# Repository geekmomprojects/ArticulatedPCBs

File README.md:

# Articulated PCBs (aka "Bendy Boards")
Design files and BOM for an articulated assembly of PCBs comprised of two-layered links that can pivot around a vertical axis, allowing the assembly to bend at every joint while still maintaining electrical contact between all of the boards in the assembly.<BR>

A demonstration of the boards and the assembly is on <a href="https://www.youtube.com/watch?v=9HDyzVgGNhk">YouTube:<BR> 
</a>

The two layers of each link connect through pressure connectors on the bottom PCB which make contact with cocentric ring-shaped pads on the top one. A laser-cut buffer layer of 1.6mm (1/16") acrylic between the two PCBs prevents the connectors from being crushed. The connectors have a working height of 1.7 mm, which prevents the connectors from being crushed between the PCBs. The layers in the link are held together with an M3 nylon push rivet. Vertical board-to-board snap connectors connect each link to the previous one in the chain. The mating height of these snap connectors is about 1.5 mm, so the spacing between the PCB layers is the same everywhere.<BR>

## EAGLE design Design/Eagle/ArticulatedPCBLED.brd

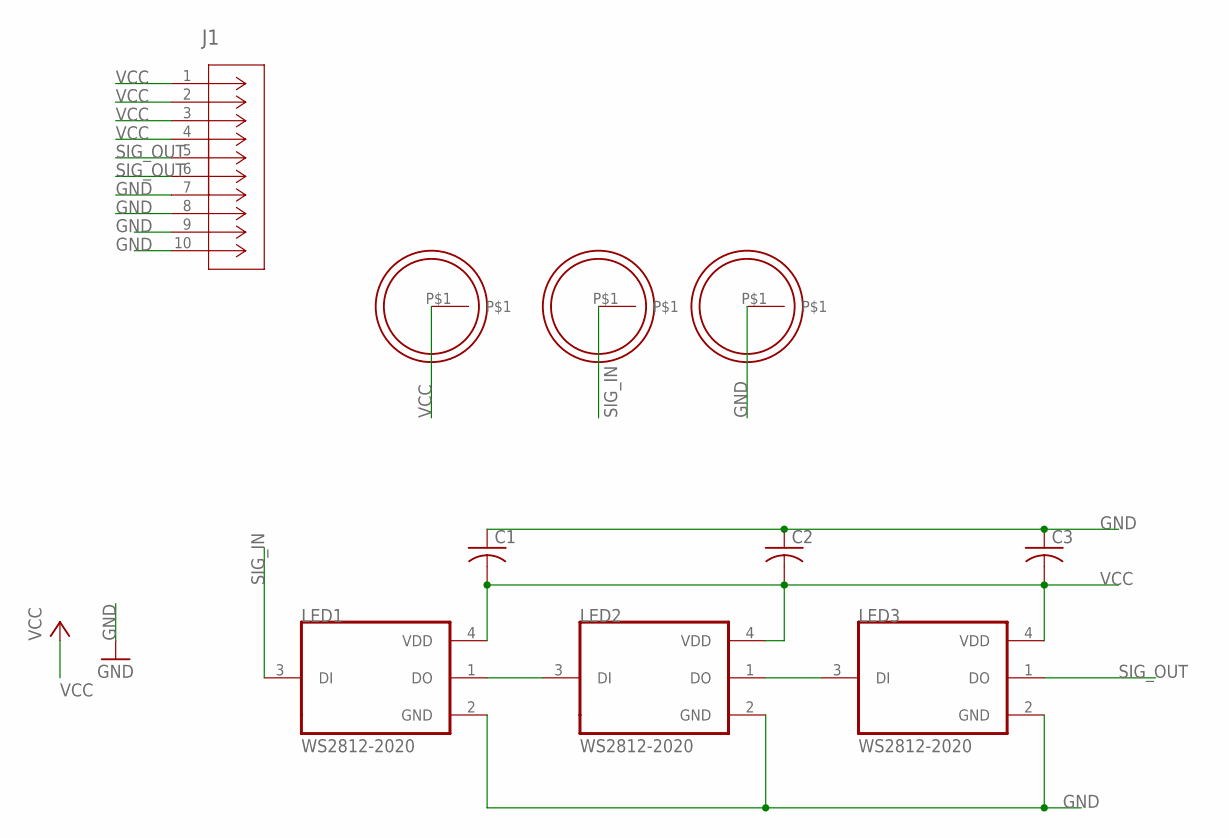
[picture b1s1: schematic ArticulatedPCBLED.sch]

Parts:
C1, C2, C3: C-USC0603; C0603
J1: DF23C-10DP-0.5V(92); CONN_DF23C-10DP-0.5V(92)_HIR
LED1, LED2, LED3: WS2812-2020; LED_WS2812-2020
U$2: CIRCLE_PAD_17_2_OD
U$3: CIRCLE_PAD_8_2_OD
U$4: CIRCLE_PAD_12_7_OD

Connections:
GND: C1.1, C2.1, C3.1, J1.7, J1.8, J1.9, J1.10, LED1.2 (GND), LED2.2 (GND), LED3.2 (GND), U$2.P$1
unnamed: LED1.1 (DO), LED2.3 (DI)
unnamed: LED2.1 (DO), LED3.3 (DI)
SIG_IN: LED1.3 (DI), U$4.P$1
SIG_OUT: J1.5, J1.6, LED3.1 (DO)
VCC: C1.2, C2.2, C3.2, J1.1, J1.2, J1.3, J1.4, LED1.4 (VDD), LED2.4 (VDD), LED3.4 (VDD), U$3.P$1

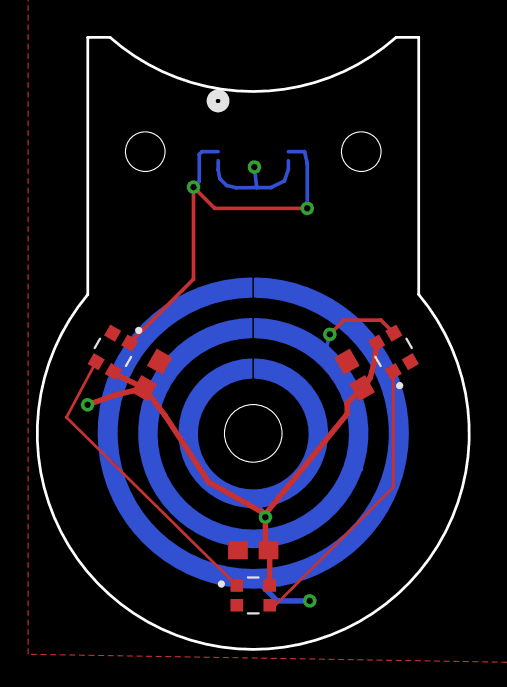
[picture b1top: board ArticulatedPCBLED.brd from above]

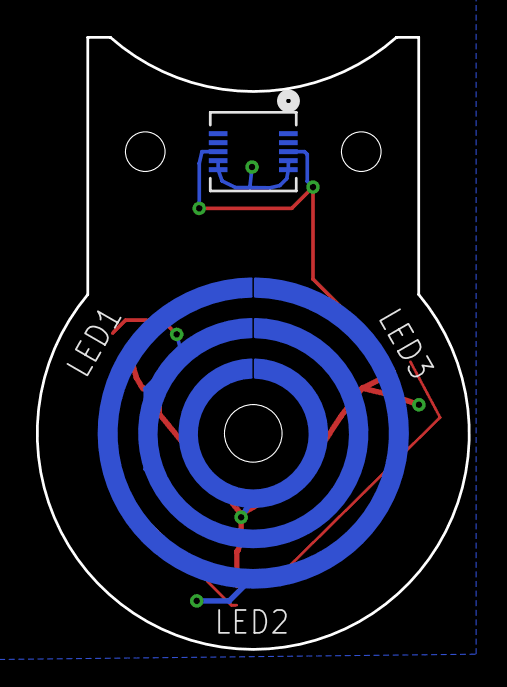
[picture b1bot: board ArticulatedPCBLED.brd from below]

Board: 2 copper layers, 24.0 x 34.0 mm, 10 parts (4 on the bottom side), 6 nets.

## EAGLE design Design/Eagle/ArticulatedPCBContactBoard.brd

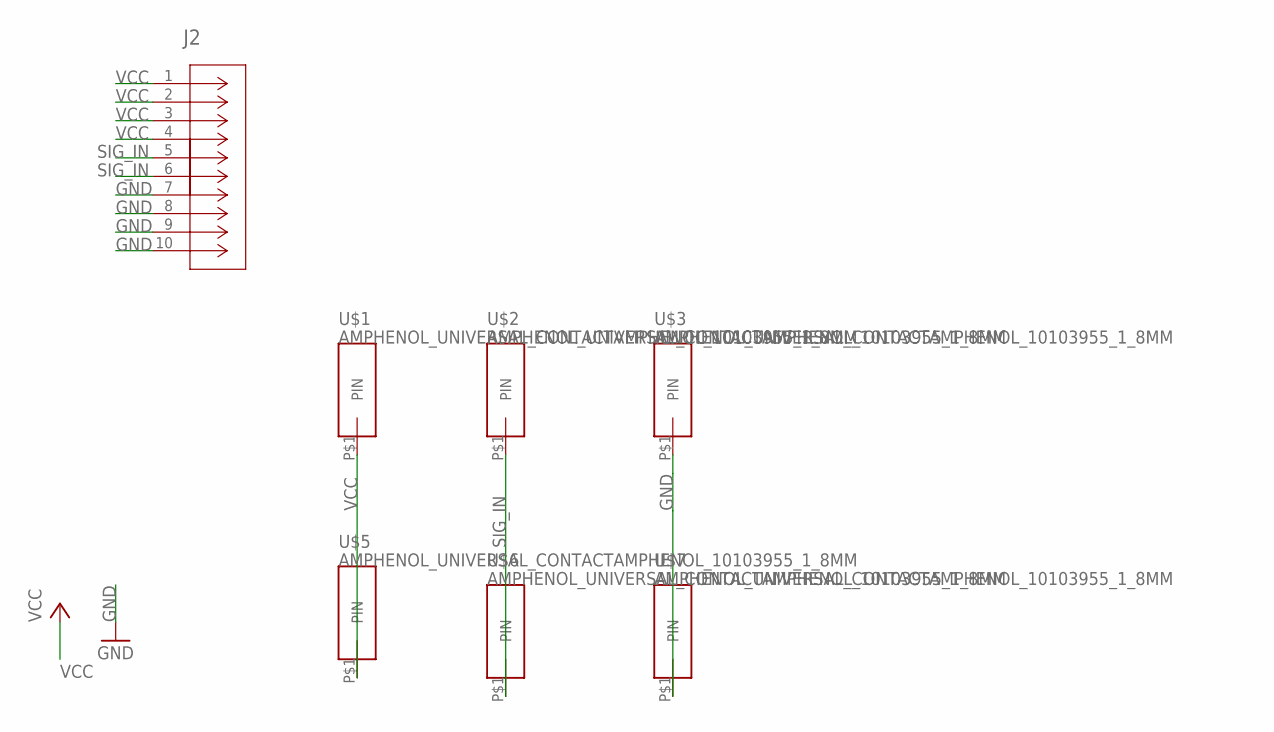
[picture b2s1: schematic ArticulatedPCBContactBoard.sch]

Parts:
J2: DF23C-10DS-0.5V(51); CONN_DF23C-10DS-0.5V(51)_HIR
U$1, U$2, U$3, U$5, U$6, U$7: AMPHENOL_UNIVERSAL_CONTACTAMPHENOL_10103955_1_8MM; AMPHENOL10103955

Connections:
GND: J2.7, J2.8, J2.9, J2.10, U$3.P$1, U$7.P$1
SIG_IN: J2.5, J2.6, U$2.P$1, U$6.P$1
VCC: J2.1, J2.2, J2.3, J2.4, U$1.P$1, U$5.P$1

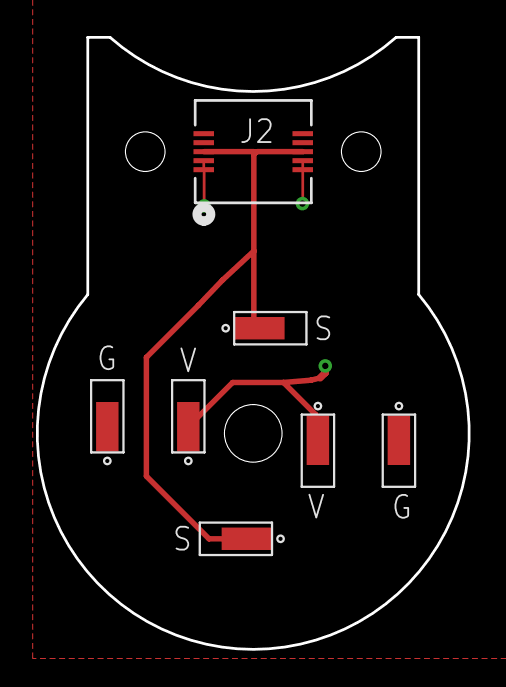
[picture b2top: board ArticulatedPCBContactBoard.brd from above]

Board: 2 copper layers, 24.0 x 34.0 mm, 7 parts (0 on the bottom side), 3 nets.

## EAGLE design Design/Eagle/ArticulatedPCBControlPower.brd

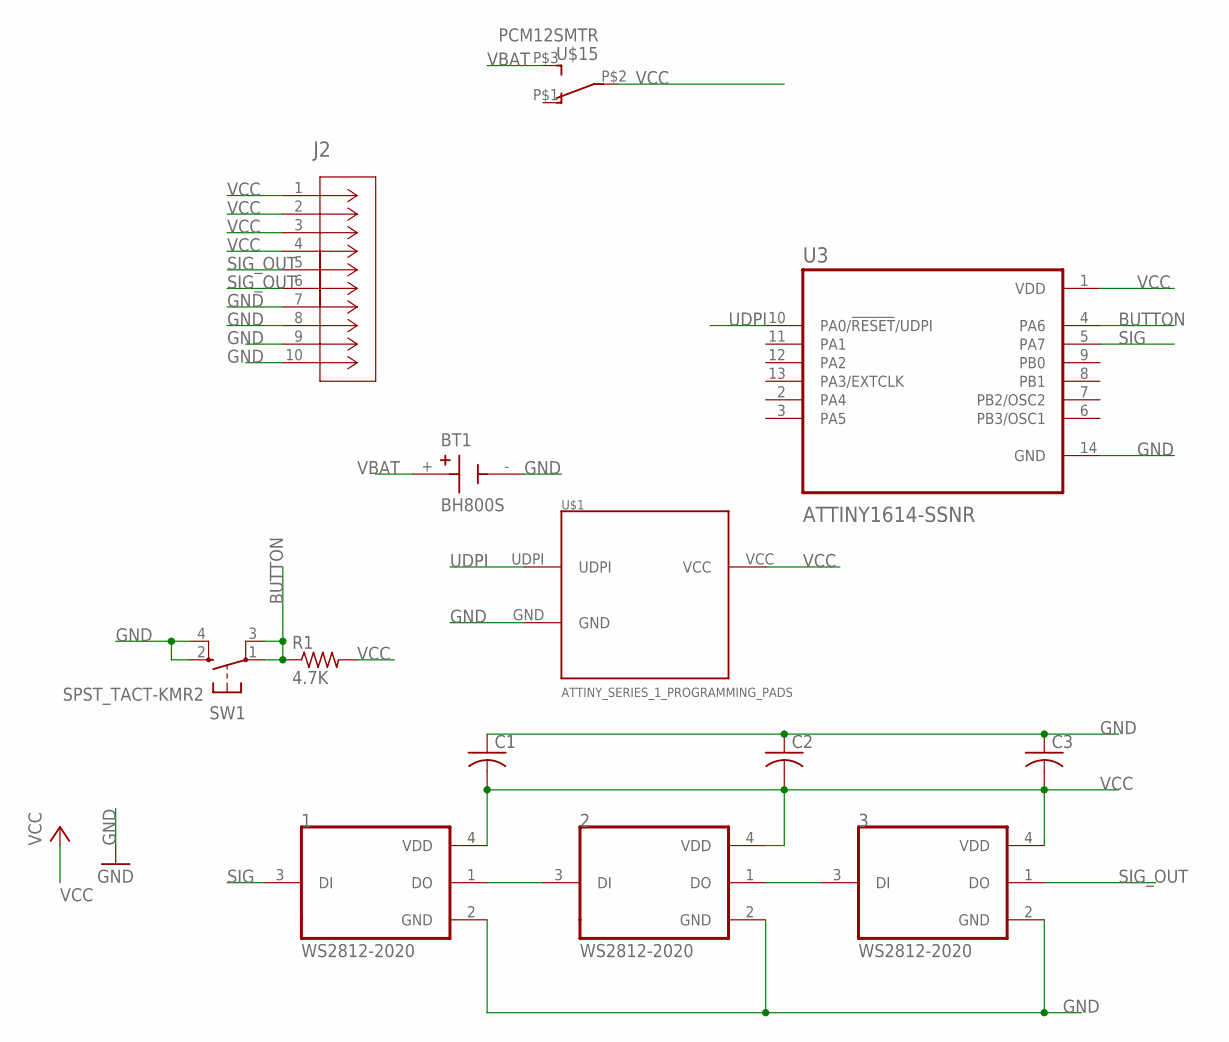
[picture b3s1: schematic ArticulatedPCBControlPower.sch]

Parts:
1, 2, 3: WS2812-2020; LED_WS2812-2020
BT1: BH800S; BAT_BH800S
C1, C2, C3: C-USC0603; C0603
J2: DF23C-10DP-0.5V(92); CONN_DF23C-10DP-0.5V(92)_HIR
R1: 4.7K; R0603
SW1: SPST_TACT-KMR2; KMR2
U3: ATTINY1614-SSNR; SOIC127P600X175-14N
U$1: ATTINY_SERIES_1_PROGRAMMING_PADS
U$15: PCM12SMTR

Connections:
BUTTON: R1.1, SW1.1, SW1.3 (P1), U3.4 (PA6)
GND: 1.2 (GND), 2.2 (GND), 3.2 (GND), BT1.-, C1.1, C2.1, C3.1, J2.7, J2.8, J2.9, J2.10, SW1.2 (S), SW1.4 (S1), U3.14 (GND), U$1.GND
unnamed: 1.1 (DO), 2.3 (DI)
unnamed: 2.1 (DO), 3.3 (DI)
SIG: 1.3 (DI), U3.5 (PA7)
SIG_OUT: 3.1 (DO), J2.5, J2.6
UDPI: U3.10 (PA0/!RESET!/UDPI), U$1.UDPI
VBAT: BT1.+, U$15.P$3 (3)
VCC: 1.4 (VDD), 2.4 (VDD), 3.4 (VDD), C1.2, C2.2, C3.2, J2.1, J2.2, J2.3, J2.4, R1.2, U3.1 (VDD), U$1.VCC, U$15.P$2 (2)

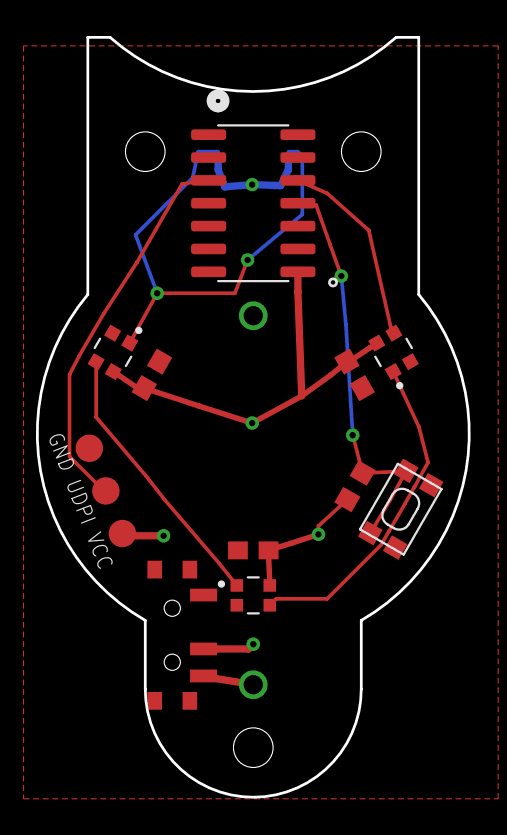
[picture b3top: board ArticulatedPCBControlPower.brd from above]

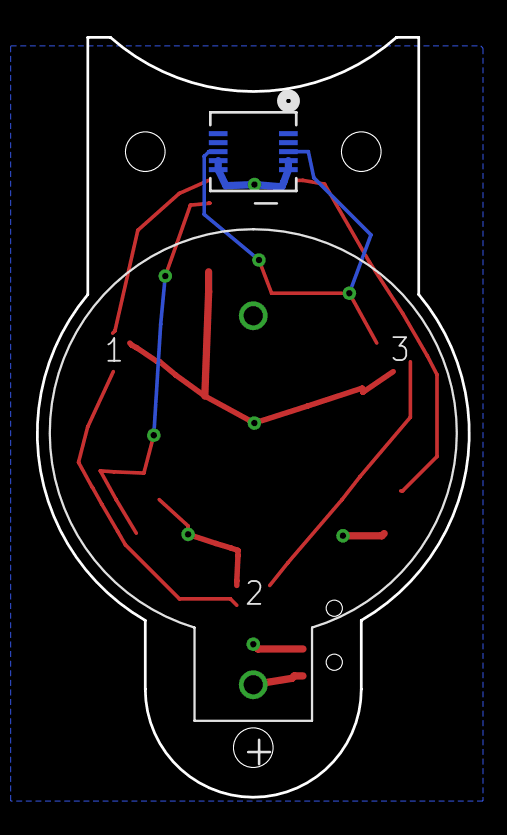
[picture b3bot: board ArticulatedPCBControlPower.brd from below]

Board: 2 copper layers, 24.0 x 42.2 mm, 13 parts (2 on the bottom side), 9 nets.

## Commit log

2021-06-02 Added BOM
2021-06-02 Add images
2021-06-02 Update BOM.xlsx
    Add board to board connectors
2021-06-02 Add acrylic buffer design
    Add SVG file for laser cutting acrylic buffer layer

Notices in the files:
parts and their libraries:
COPYRIGHT: Copyright (C) 2018 Accelerated Designs. All rights reserved
